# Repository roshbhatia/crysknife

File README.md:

# crysknife

A 42-key wireless split keyboard with MX hotswap sockets, ZMK firmware, and a 750 mAh battery in each half.
It uses nice!nano V2 controllers, white PCBs, and a knife illustration and poem lines on both PCB faces.

## PCB

<details open>
<summary>Front</summary>

</details>

<details>
<summary>Back</summary>

</details>

## Case

Each half uses two rigid plates, four M2 standoffs, and a removable TPU sleeve.
The sleeve has a closed bottom and a lip that grips the top plate. USB, power, and reset have side openings.

The printed version uses translucent resin plates. The top keeps 1.6 mm switch seats and adds a narrow underside rim.
Flat acrylic tops and aluminum bottoms are an alternative from SendCutSend.

Compare [four enclosure alternatives](manufacturing/enclosures/README.md): CNC plates with TPU, CNC trays, printed cases, and gasket hybrids.

## Edit the design

- [Layout](ergogen/layout.yaml): key spacing and column stagger.
- [PCB models](tscircuit/README.md#edit-the-models): open either half in the tscircuit editor.
- [Case model](case/sandwich.scad): open in OpenSCAD; dimensions live in [parameters.scad](case/parameters.scad).
- [Artwork](assets/knife.svg): the original knife illustration. All PCB text uses Ioskeley Mono Bold.

[previews/](previews/) contains images of both PCB faces and the case.
[out/](out/README.md) contains checked KiCad projects, schematics, firmware, and 3D models.

## Build

Enter the Nix shell, then install the locked dependencies:

```sh
nix develop .
npm ci
npm ci --prefix tscircuit
```

Generate the boards, artwork, routing, schematics, and case:

```sh
npm run pcb
python3 scripts/add_artwork.py
npm run route
python3 scripts/check_electrical.py
python3 scripts/generate_schematic.py
python3 scripts/generate_assembly.py
python3 scripts/check_assembly_guards.py
python3 scripts/check_supplier_placement.py
npm run case
python3 scripts/check_case_models.py
python3 scripts/export_printed_case.py
python3 scripts/save_previews.py
```

Ergogen generates the layout. tscircuit routes the boards. KiCad checks the finished copper and schematic in GitHub Actions.
A separate workflow builds the left, right, and settings-reset firmware.

## Assembly and ordering

JLCPCB files are in [manufacturing/jlcpcb/](manufacturing/jlcpcb/README.md).
SendCutSend files are in [manufacturing/sendcutsend/](manufacturing/sendcutsend/README.md).
Printed case files are in [manufacturing/jlc3dp/](manufacturing/jlc3dp/README.md).
The [assembly guide](manufacturing/README.md) lists parts, controller headers, battery connections, and soldering work.

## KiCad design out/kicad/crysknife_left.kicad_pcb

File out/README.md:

# Engineering exports

- `kicad/`: editable routed boards, complete schematics, local libraries, schematic PDFs, and exported netlists.
- `3d/`: active 750 mAh reinforced resin tops, resin bottoms, metal bottoms with RF windows, rigid assemblies, and shortened TPU sleeves in 3MF format.
- `../manufacturing/enclosures/f-750-rigid-sandwich/`: active aluminum-floor STEP/STL/DXF, PMMA RF inserts, top plates, and hardware.
- `firmware/`: verified UF2 builds for each half and settings reset.
- `validation.json`: PCB check revision, reports, and board hashes.

Open `kicad/crysknife_left.kicad_pro` or `kicad/crysknife_right.kicad_pro` in KiCad.
Open `case/sandwich.scad` from the repository root for the parameter-based mechanical source.
The 3MF files are exported geometry. Edit the OpenSCAD source to change the case.
Read `tscircuit/README.md` for live React editing.

Regeneration replaces these snapshots. Keep lasting changes in the source generators and parameter files.
Fresh images live in `previews/`. Supplier files live in `manufacturing/jlcpcb/`, `manufacturing/jlc3dp/`, and `manufacturing/sendcutsend/`.

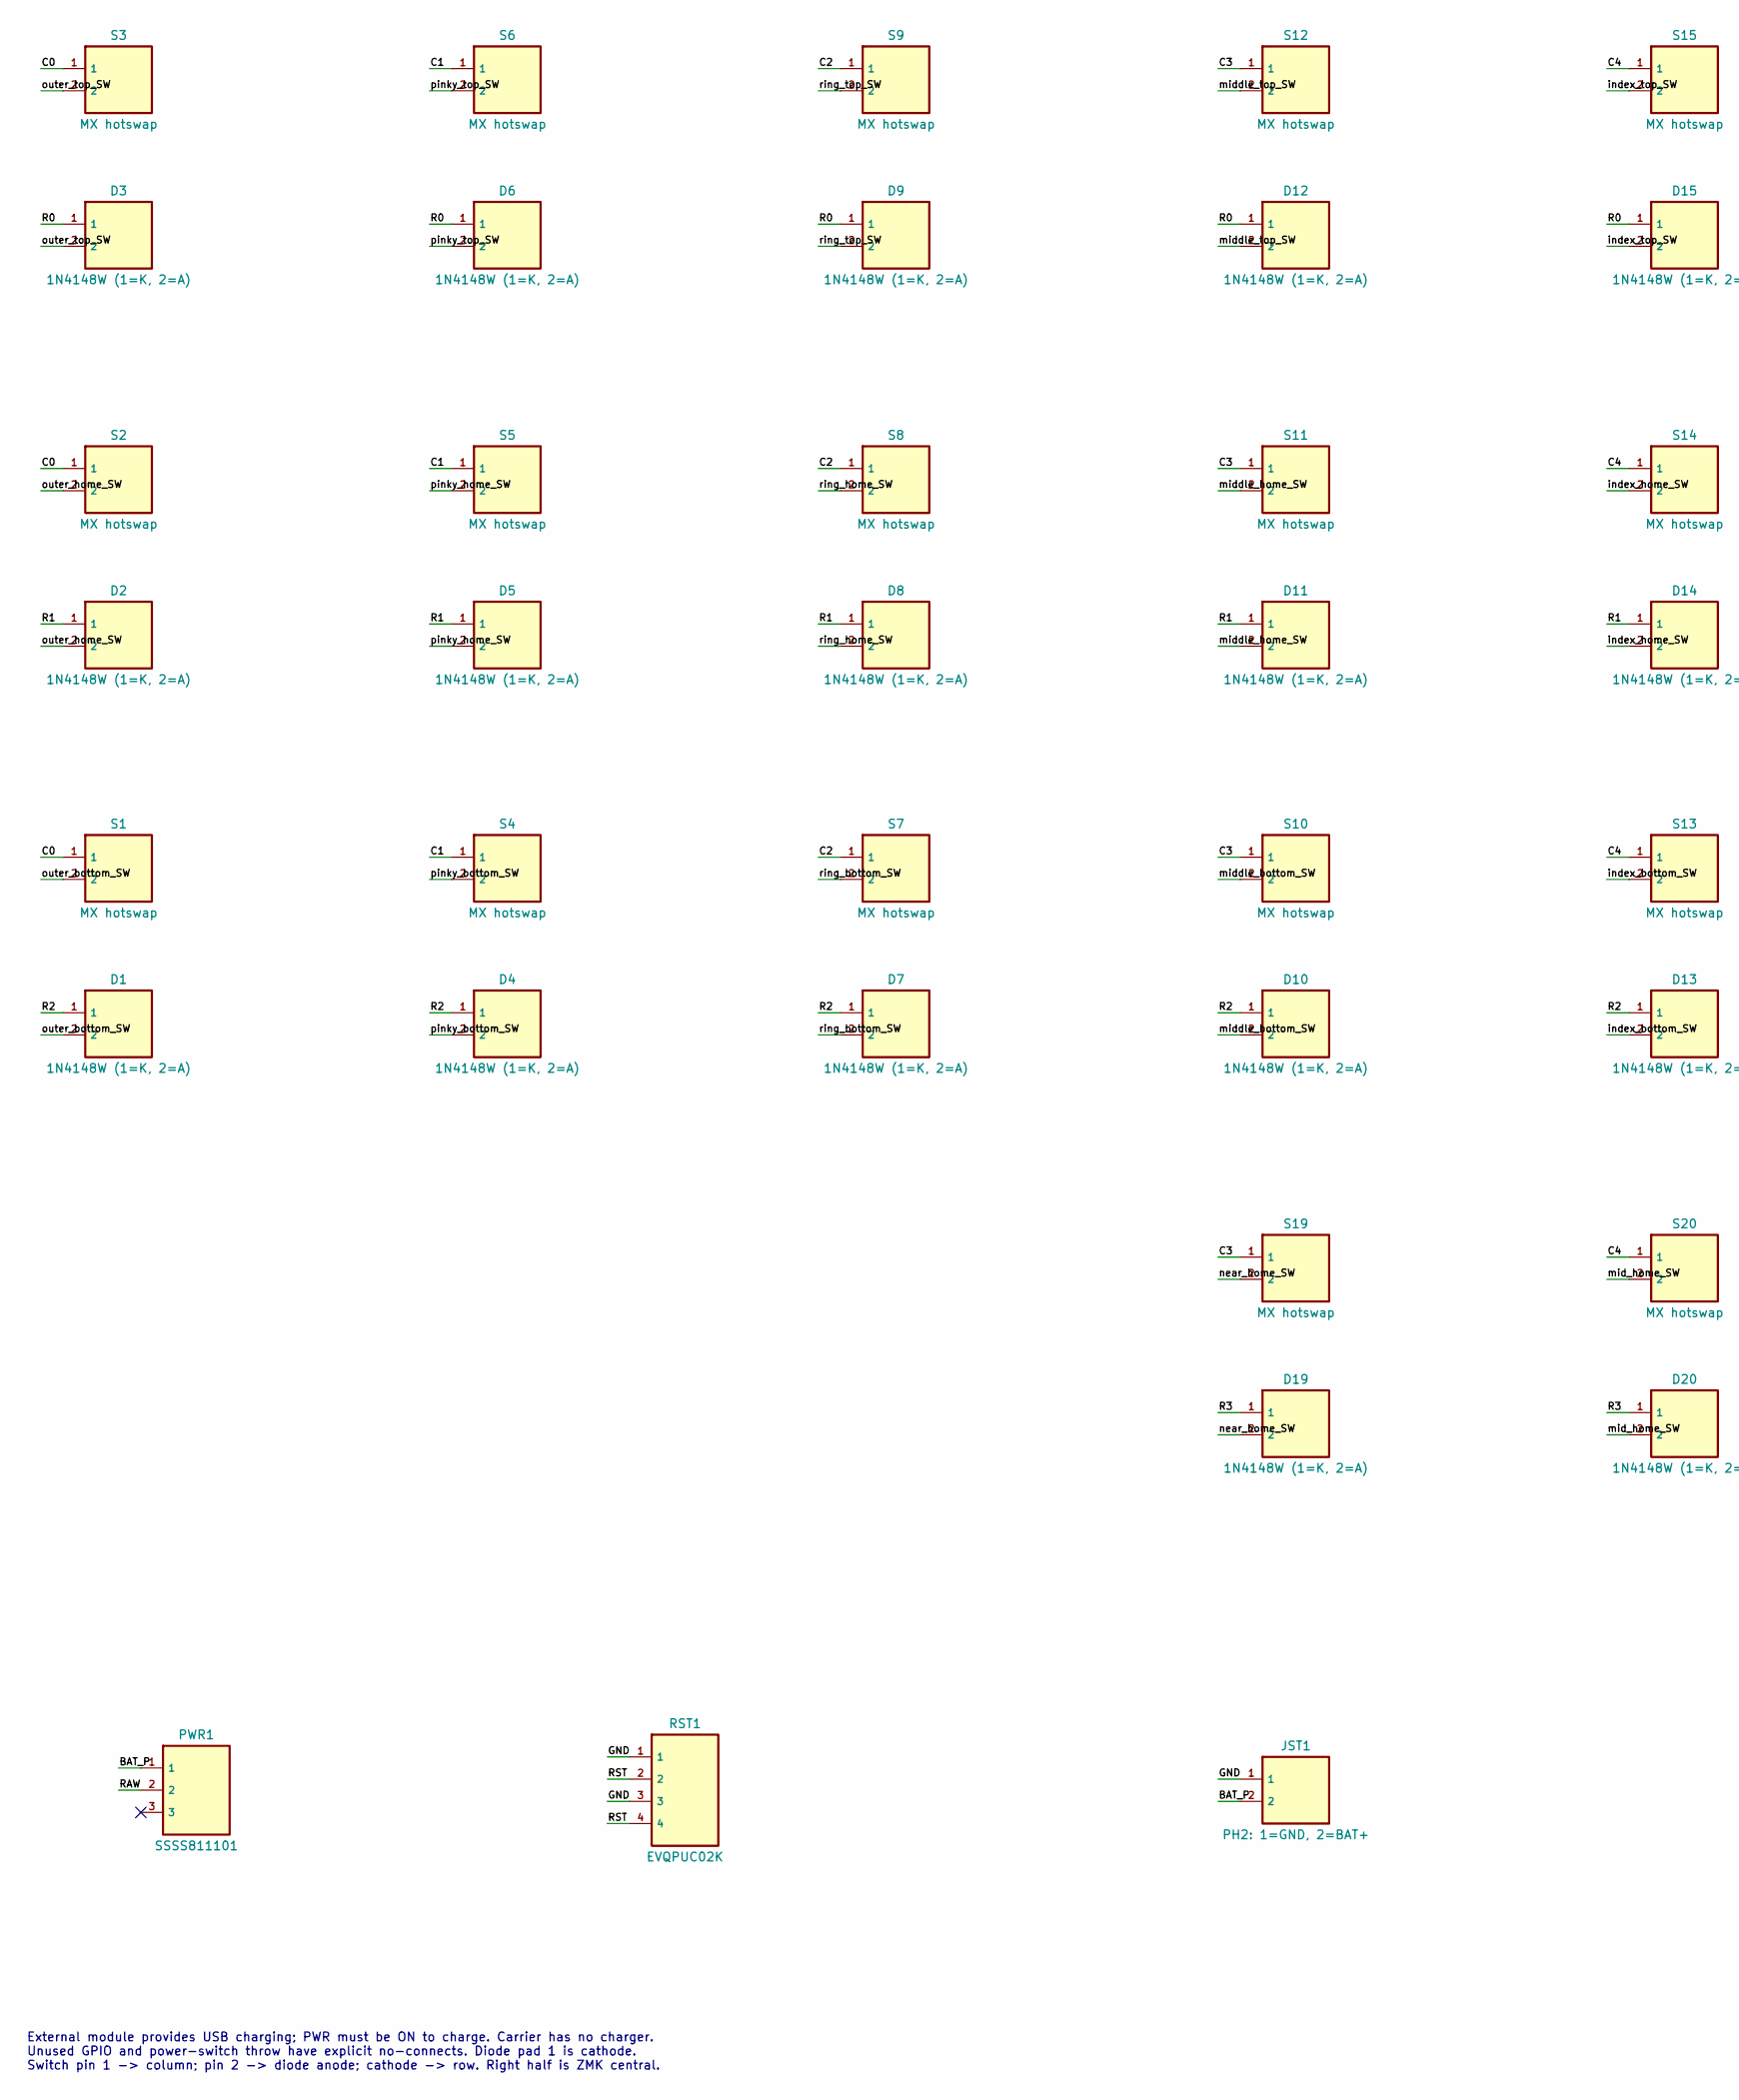
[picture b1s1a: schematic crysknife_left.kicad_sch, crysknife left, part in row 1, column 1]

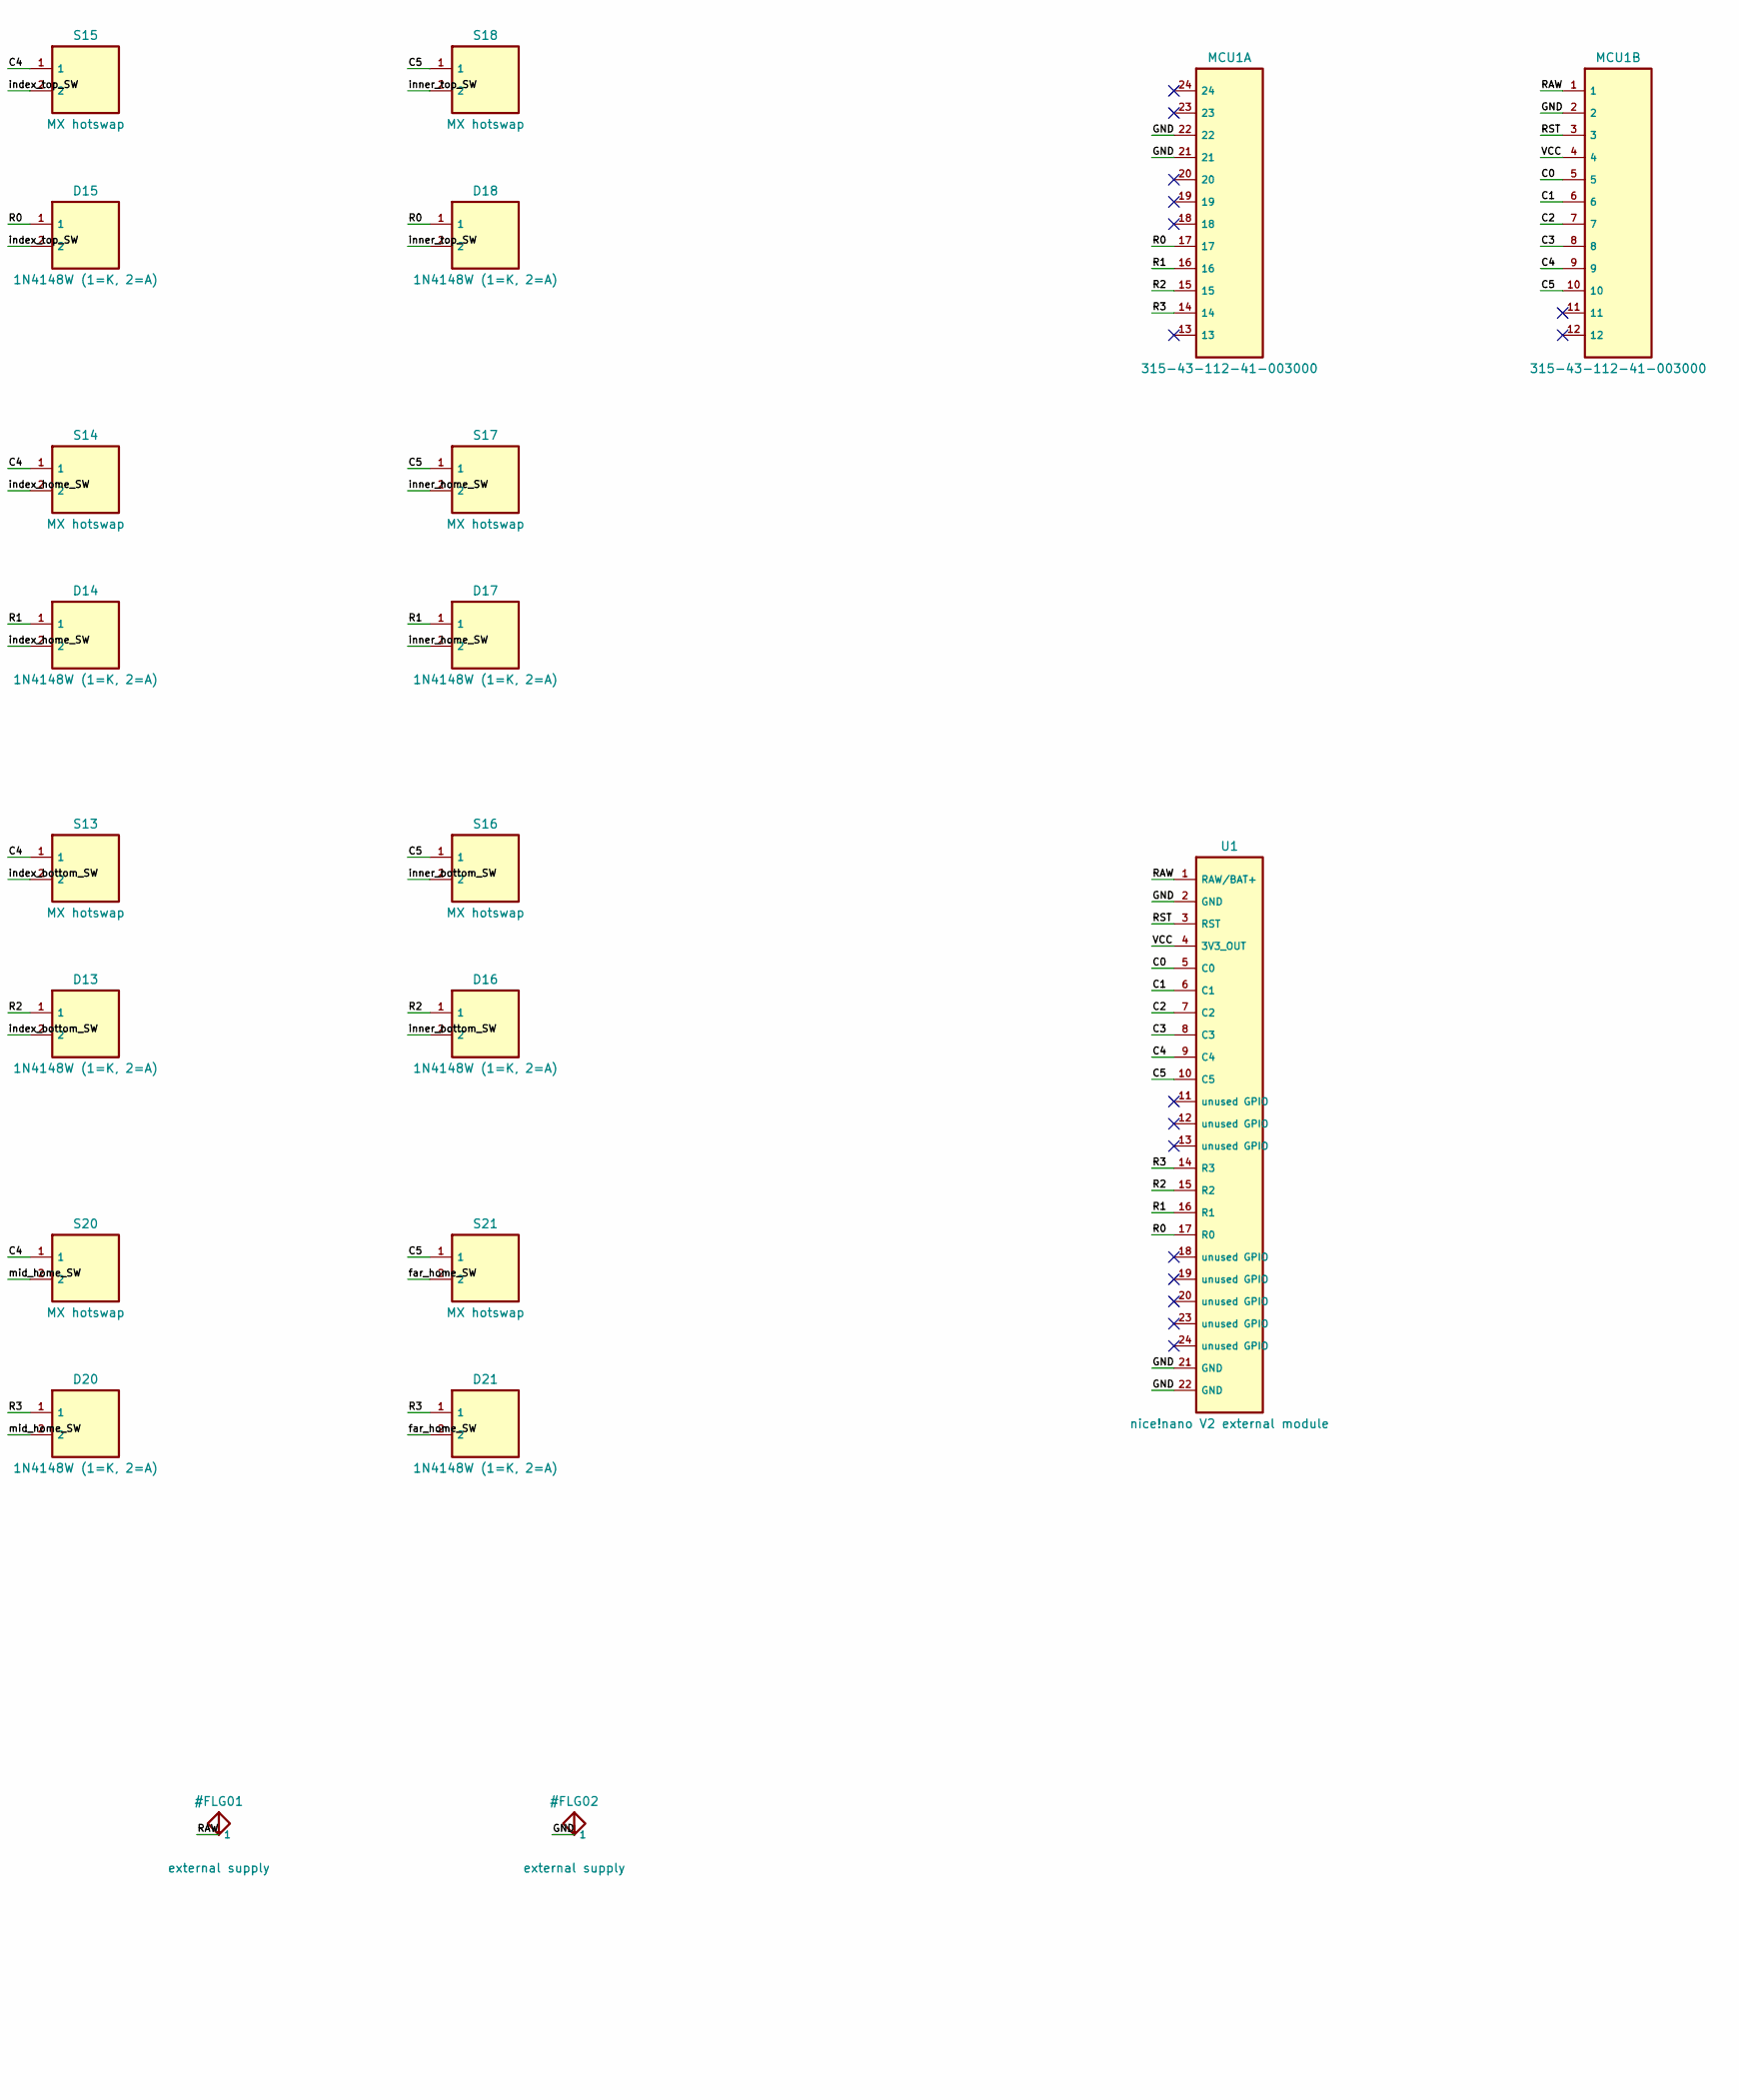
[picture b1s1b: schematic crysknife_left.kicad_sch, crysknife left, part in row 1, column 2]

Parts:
D1: 1N4148W (1=K, 2=A); D1
D2: 1N4148W (1=K, 2=A); D2
D3: 1N4148W (1=K, 2=A); D3
D4: 1N4148W (1=K, 2=A); D4
D5: 1N4148W (1=K, 2=A); D5
D6: 1N4148W (1=K, 2=A); D6
D7: 1N4148W (1=K, 2=A); D7
D8: 1N4148W (1=K, 2=A); D8
D9: 1N4148W (1=K, 2=A); D9
D10: 1N4148W (1=K, 2=A); D10
D11: 1N4148W (1=K, 2=A); D11
D12: 1N4148W (1=K, 2=A); D12
D13: 1N4148W (1=K, 2=A); D13
D14: 1N4148W (1=K, 2=A); D14
D15: 1N4148W (1=K, 2=A); D15
D16: 1N4148W (1=K, 2=A); D16
D17: 1N4148W (1=K, 2=A); D17
D18: 1N4148W (1=K, 2=A); D18
D19: 1N4148W (1=K, 2=A); D19
D20: 1N4148W (1=K, 2=A); D20
D21: 1N4148W (1=K, 2=A); D21
JST1: PH2: 1=GND, 2=BAT+; JST1
MCU1A: 315-43-112-41-003000; MCU1A
MCU1B: 315-43-112-41-003000; MCU1B
PWR1: SSSS811101; PWR1
RST1: EVQPUC02K; RST1
S1: MX hotswap; S1
S2: MX hotswap; S2
S3: MX hotswap; S3
S4: MX hotswap; S4
S5: MX hotswap; S5
S6: MX hotswap; S6
S7: MX hotswap; S7
S8: MX hotswap; S8
S9: MX hotswap; S9
S10: MX hotswap; S10
S11: MX hotswap; S11
S12: MX hotswap; S12
S13: MX hotswap; S13
S14: MX hotswap; S14
S15: MX hotswap; S15
S16: MX hotswap; S16
S17: MX hotswap; S17
S18: MX hotswap; S18
S19: MX hotswap; S19
S20: MX hotswap; S20
S21: MX hotswap; S21
U1: nice!nano V2 external module

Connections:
BAT_P: JST1.2, PWR1.1
C0: MCU1B.5, S1.1, S2.1, S3.1, U1.5 (C0)
C1: MCU1B.6, S4.1, S5.1, S6.1, U1.6 (C1)
C2: MCU1B.7, S7.1, S8.1, S9.1, U1.7 (C2)
C3: MCU1B.8, S10.1, S11.1, S12.1, S19.1, U1.8 (C3)
C4: MCU1B.9, S13.1, S14.1, S15.1, S20.1, U1.9 (C4)
C5: MCU1B.10, S16.1, S17.1, S18.1, S21.1, U1.10 (C5)
GND: JST1.1, MCU1A.21, MCU1A.22, MCU1B.2, RST1.1, RST1.3, U1.2 (GND), U1.21 (GND), U1.22 (GND)
P0: MCU1A.23
P1: MCU1A.24
P2: MCU1A.20
P3: MCU1A.19
P4: MCU1A.18
P9: MCU1A.13
P10: MCU1B.12
P16: MCU1B.11
R0: D3.1, D6.1, D9.1, D12.1, D15.1, D18.1, MCU1A.17, U1.17 (R0)
R1: D2.1, D5.1, D8.1, D11.1, D14.1, D17.1, MCU1A.16, U1.16 (R1)
R2: D1.1, D4.1, D7.1, D10.1, D13.1, D16.1, MCU1A.15, U1.15 (R2)
R3: D19.1, D20.1, D21.1, MCU1A.14, U1.14 (R3)
RAW: MCU1B.1, PWR1.2, U1.1 (RAW/BAT+)
RST: MCU1B.3, RST1.2, RST1.4, U1.3 (RST)
VCC: MCU1B.4, U1.4 (3V3_OUT)
far_home_SW: D21.2, S21.2
index_bottom_SW: D13.2, S13.2
index_home_SW: D14.2, S14.2
index_top_SW: D15.2, S15.2
inner_bottom_SW: D16.2, S16.2
inner_home_SW: D17.2, S17.2
inner_top_SW: D18.2, S18.2
mid_home_SW: D20.2, S20.2
middle_bottom_SW: D10.2, S10.2
middle_home_SW: D11.2, S11.2
middle_top_SW: D12.2, S12.2
near_home_SW: D19.2, S19.2
outer_bottom_SW: D1.2, S1.2
outer_home_SW: D2.2, S2.2
outer_top_SW: D3.2, S3.2
pinky_bottom_SW: D4.2, S4.2
pinky_home_SW: D5.2, S5.2
pinky_top_SW: D6.2, S6.2
ring_bottom_SW: D7.2, S7.2
ring_home_SW: D8.2, S8.2
ring_top_SW: D9.2, S9.2

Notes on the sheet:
External module provides USB charging; PWR must be ON to charge. Carrier has no charger. Unused GPIO and power-switch throw have explicit no-connects. Diode pad 1 is cathode. Switch pin 1 -> column; pin 2 -> diode anode; cathode -> row. Right half is ZMK central.

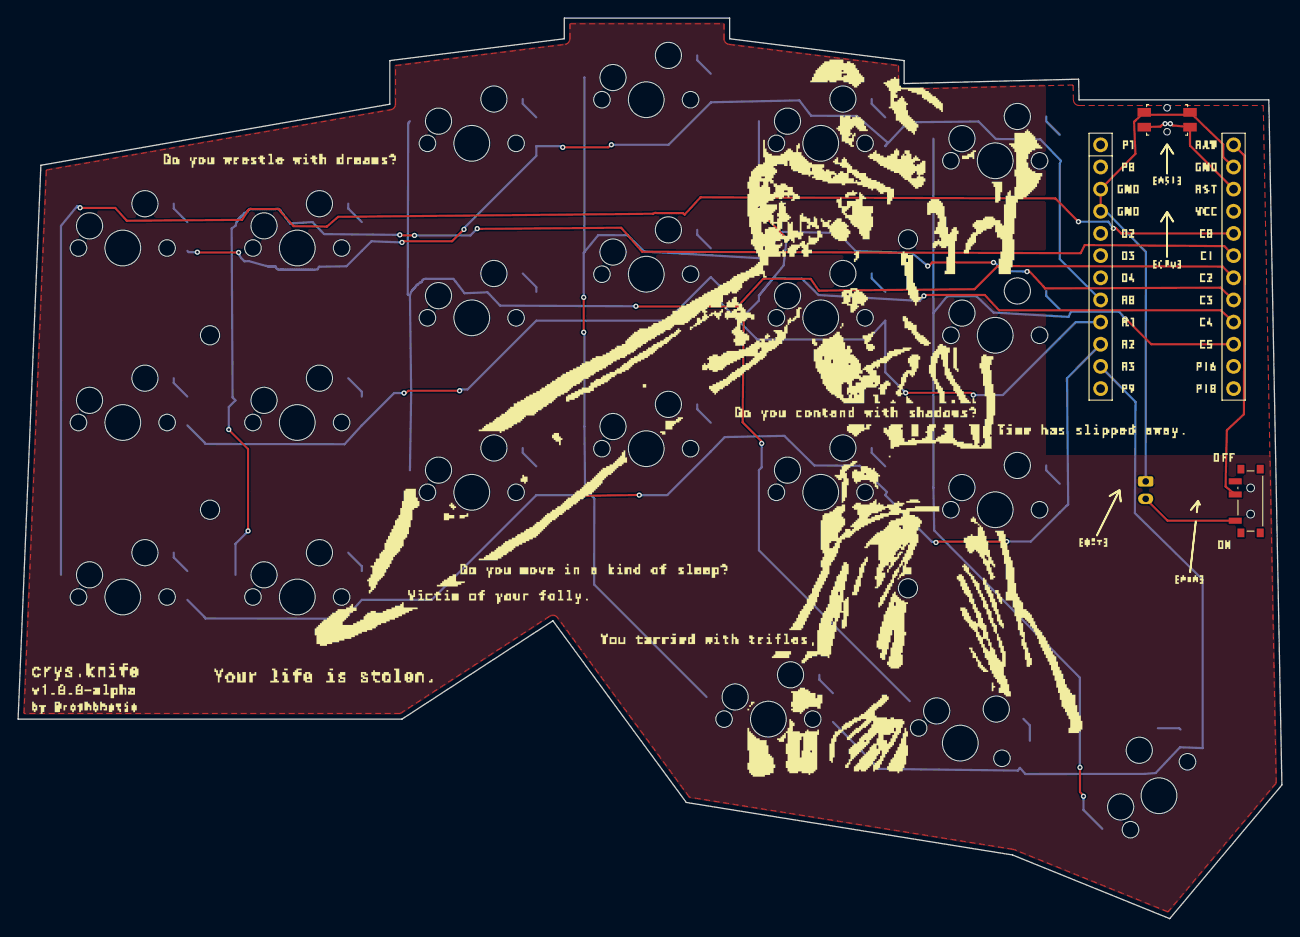
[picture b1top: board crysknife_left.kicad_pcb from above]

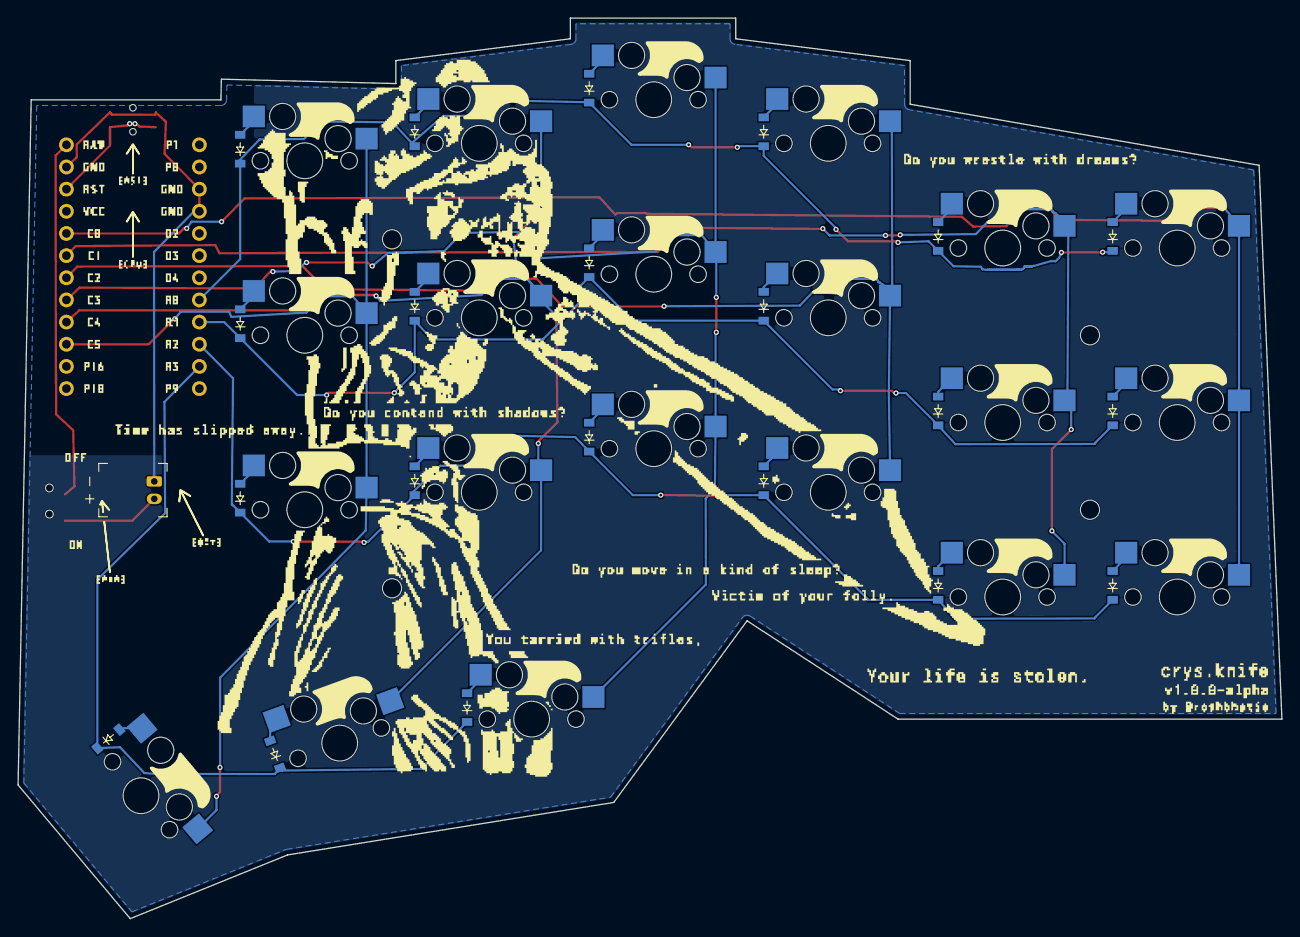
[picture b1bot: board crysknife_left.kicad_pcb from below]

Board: 2 copper layers, 144.9 x 103.2 mm, 53 parts (45 on the bottom side), 35 nets.

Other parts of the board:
ART1: knife-silkscreen
MCU1: mcu_nice_nano
MH1, MH2, MH3, MH4: mounting_hole_npth
